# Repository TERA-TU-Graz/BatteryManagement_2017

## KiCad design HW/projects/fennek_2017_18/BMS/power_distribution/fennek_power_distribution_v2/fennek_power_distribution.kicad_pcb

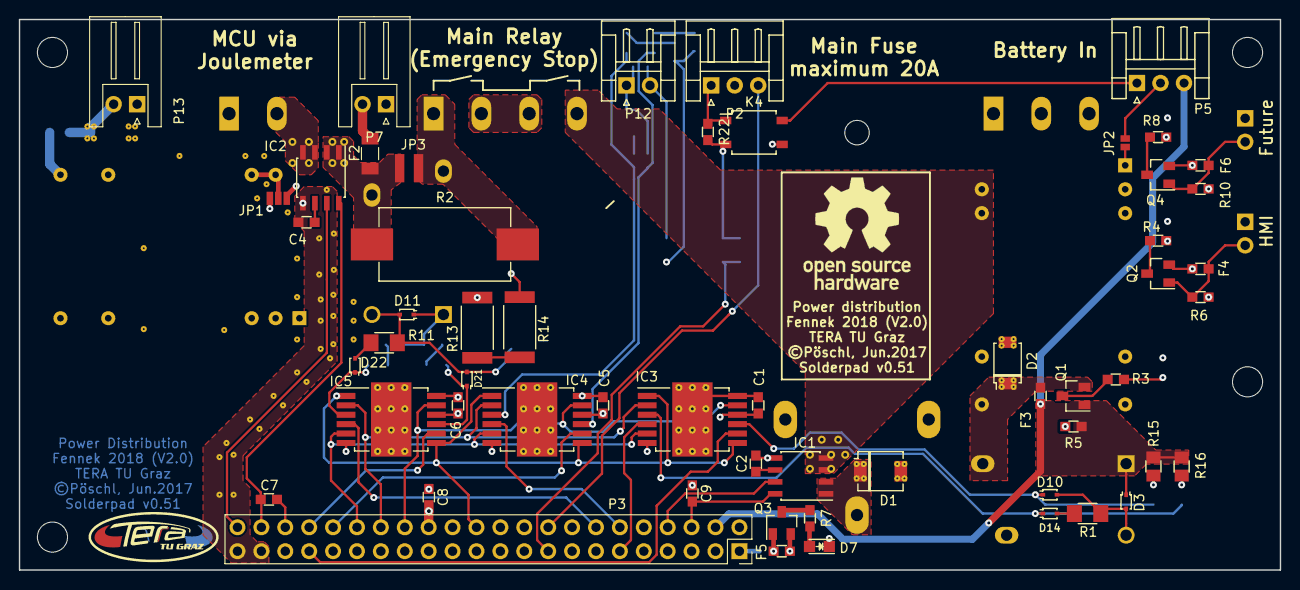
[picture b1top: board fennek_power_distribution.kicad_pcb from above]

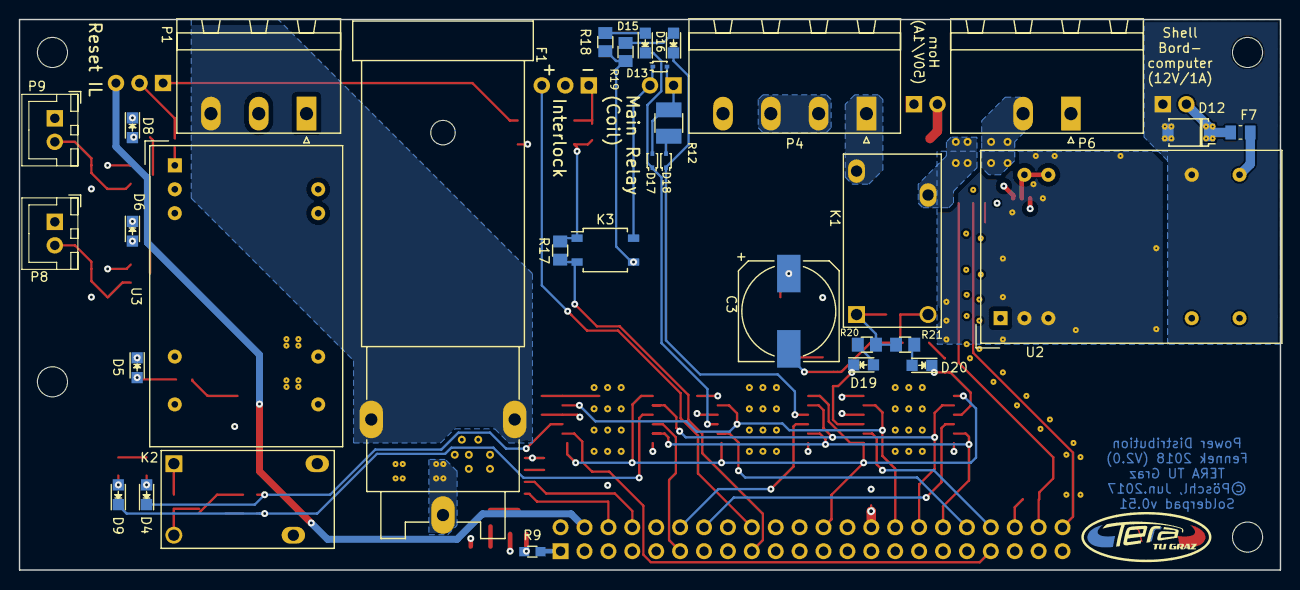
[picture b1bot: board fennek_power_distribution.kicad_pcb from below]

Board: 4 copper layers, 134.0 x 58.5 mm, 91 parts (34 on the bottom side), 71 nets.

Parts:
C1, C5, C6, C7, C8, C9: 100n; C_0603in
C2, C4: 1nf; C_0603in
C3: 820u; c_elec_10x10mm
D1: 58V; DO-214AA_with_vias_in_pad
D2, D12: 14V; SOD128_with_vias_in_pad
D3, D10, D11, D13, D14, D17, D18, D21, D22: BAS3005B-02V; BAS3005B-02V__sc79
D4, D15, D19: K_CH1; LED_0805
D5: BMS_crtl_blown; LED_0805
D6: HMI_blown; LED_0805
D7: BMS_pwr_blown; LED_0805
D8: Future_blown; LED_0805
D9, D16, D20: K_CH2; LED_0805
F1: 20A 60VDC; Fuse_holder_6.3x32mm_Schruter_0031.2520
F2: 1A 63VDC; Fuse_1206_3216Metric_Pad1.24x1.80mm_HandSolder
F3, F4, F5, F6: 0.5A 12VDC; Fuse_0603in
F7: 1A 12VDC; Fuse_0805_2012Metric_Pad1.15x1.50mm_HandSolder
IC1, IC2: ACS722LLCTR-20AB-T; ACS7xx
IC3, IC4, IC5: TLE8102SG; INF-PG-DSO-12-11-EP_N_EPvias
JP1: SEM_source; SOLDERJUMPER_3
JP2: Jumper_NO_Small; SOLDERJUMPER_2_1mm
JP3: Jumper_NO_Small; SOLDERJUMPER_2_3mm_HV
K1, K2: TE_OJ-SH-112DM; RELAIS-TE-OJ
K3: ASSR-1218; SO-4
K4: Panasonic_AQY414S; SO-4
P1: HV_in; PhoenixContact_MSTBA-G_03x5.08mm_Angled
P2: Interlock; JST_EH_S03B-EH_03x2.50mm_Angled
P3: CONN_02X22; ESW-122-12-L-D
P4: HV_Emergency_Stop_Relay; PhoenixContact_MSTBA-G_04x5.08mm_Angled
P5: Reset_Interlock; JST_EH_S03B-EH_03x2.50mm_Angled
P6: MCU_HV_supply; PhoenixContact_MSTB-GF_02x5.08mm_Angled_ThreadedFlange
P7: Horn; JST_XH_S02B-XH-A_02x2.50mm_Angled
P8: HMI_supply; JST_XH_B02B-XH-A_02x2.50mm_Straight
P9: Future_use; JST_XH_B02B-XH-A_02x2.50mm_Straight
P12: Main_relay_coil; JST_EH_S02B-EH_02x2.50mm_Angled
P13: SEM_telemetry_supply; JST_XH_S02B-XH-A_02x2.50mm_Angled
Q1, Q2, Q3, Q4: IRLML2246TRPBF-1
R1, R11: 180R; R_1206in
R2: 470R 5W; TE_SMW-5W
R3, R4, R7, R8: 12k; R_0603in
R5, R6, R9, R10: 100k; R_0603in
R12: 10R 500mW; R_1210in
R13, R14: 22R 2W; R_2512in
R15, R16, R18, R19, R20, R21: 12k; R_0805in
R17: 1k; R_0805in
R22: 1k; R_0603in
U2, U3: THD_12-4812_single_output; THD_12-xxxx
svg2mod, svg2mod#2: G***; TERA_Logo_SilkS_and_Cu_5x12.5mm

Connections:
/12VDC Bordnet/12V_Relay_Fault: IC3.4, P3.11
/12VDC Bordnet/+5V: C1.2, C5.2, C6.2, C8.2, IC3.10, IC4.10, IC5.10, P3.28
/12VDC Bordnet/+12VDC: D2.1, F3.1, K2.11, Q1.2, U3.14
/12VDC Bordnet/+12V_Future: F6.2, P9.2, Q4.1, R10.1
/12VDC Bordnet/+12V_HMI: F4.2, P8.2, Q2.1, R6.1
/12VDC Bordnet/+12V_switched: F4.1, F5.1, F6.1, K2.14, Q2.2, Q3.2, Q4.2
/12VDC Bordnet/BN_IL: K4.4, P5.1
/12VDC Bordnet/BN_on: JP2.1, P5.2
/12VDC Bordnet/IL_next-: K4.1, P2.1, R22.1
/12VDC Bordnet/Interlock_OK: IC3.1, IC3.7, IC4.1, IC4.7, IC5.1, IC5.7, P3.24
/12VDC Bordnet/LowSideSwitch_12V_Relay/CHANNEL1: D3.2, D10.2, K2.A2, R1.1
/12VDC Bordnet/LowSideSwitch_12V_Relay/CHANNEL2: D14.2, R1.2
/12VDC Bordnet/MISO: IC3.11, IC4.11, IC5.11, P3.30
/12VDC Bordnet/MOSI: IC3.2, IC4.2, IC5.2, P3.32
/12VDC Bordnet/NCS_12V_Relay: IC3.8, P3.37
/12VDC Bordnet/SCLK: IC3.5, IC4.5, IC5.5, P3.34
/12VDC telemetry/+12V_telemetry: D12.1, F7.2, P13.2
/12VDC telemetry/GND_telemetry: D12.2, P13.1, U2.16
/High voltage/+3V3: C7.2, C9.2, IC1.8, IC2.8, P3.6, P3.42
/High voltage/+HV_in: F1.2, P1.3
/High voltage/+VBatt: IC1.3, IC1.4, JP1.3, P4.4, U3.22, U3.23
/High voltage/HV+_Main_Relays: P4.2, P4.3
/High voltage/HV+_after_main_relais: JP3.1, K1.11, P4.1, R2.2
/High voltage/HV+_fused: D1.1, F1.1, IC1.1, IC1.2
/High voltage/HV+_to_MCU: IC2.3, IC2.4, P6.2
/High voltage/IL_next-: K3.1, K4.2, R17.2, R22.2
/High voltage/ISense_MCU: IC2.7, P3.44
/High voltage/ISense_Main: IC1.7, P3.8
/High voltage/LowSideSwitch_MainRelay/CHANNEL2: D18.2, R12.2
/High voltage/LowSideSwitch_PreCharge/CHANNEL2: D22.2, R11.2
/High voltage/MainRelay_Fault: IC4.4, P3.12
/High voltage/Main_Relay_A1: D13.1, K3.4, P12.2
/High voltage/Main_Relay_A2: D13.2, D17.2, P12.1, R12.1
/High voltage/NCS_MainRelay: IC4.8, P3.36
/High voltage/PreCharge_Fault: IC5.4, P3.14
/High voltage/PreCharger_A2: C3.2, D11.2, D21.2, K1.A2, R11.1
/High voltage/V+_Horn: F2.2, P7.2
/High voltage/VBatt_Switched: F2.1, IC2.1, IC2.2, JP1.1, JP3.2, K1.14, R2.1
/Master Connector/+12VDC_BMS: D3.1, F3.2, K2.A1, P3.4, P5.3, Q1.1, R5.1, R15.1, R16.1
/Master Connector/+12VDC_BMS_Switched: D11.1, F5.2, K1.A1, K3.3, P3.2, Q3.1, R9.1, R13.2, R18.1, R19.1, R20.1, R21.1
/Master Connector/IL_master+: P2.3, P3.18
/Master Connector/IL_master-: K3.2, P3.17, R17.1
/Master Connector/NCS_PreCharge: IC5.8, P3.38
GND: C1.1, C2.2, C4.2, C5.1, C6.1, C7.1, C8.1, C9.1, D1.2, D2.2, D5.1, D6.1, D7.1, D8.1, IC1.5, IC2.5, IC3.6, IC3.12, IC3.13, IC4.6, IC4.12, IC4.13, IC5.6, IC5.12, IC5.13, K4.3, P1.1, P3.1, P3.3, P3.5, P3.7, P3.9, P3.10, P3.13, P3.21, P3.22, P3.23, P3.25, P3.26, P3.27, P3.29, P3.31, P3.33, P3.35, P3.39, P3.40, P3.41, P3.43, P6.1, P7.1, P8.1, P9.1, R5.2, R6.2, R9.2, R10.2, U2.2, U2.3, U3.2, U3.3, U3.16
unnamed: C2.1, IC1.6
unnamed: C3.1, R14.1
unnamed: C4.1, IC2.6
unnamed: D4.2, R15.2
unnamed: D5.2, R3.2
unnamed: D6.2, R4.2
unnamed: D7.2, R7.2
unnamed: D8.2, R8.2
unnamed: D9.2, R16.2
unnamed: D4.1, D10.1, IC3.9
unnamed: D9.1, D14.1, IC3.3
unnamed: D15.1, D17.1, IC4.9
unnamed: D15.2, R18.2
unnamed: D16.1, D18.1, IC4.3
unnamed: D16.2, R19.2
unnamed: D19.1, D21.1, IC5.9
unnamed: D19.2, R20.2
unnamed: D20.1, D22.1, IC5.3
unnamed: D20.2, R21.2
unnamed: F7.1, U2.14
unnamed: JP1.2, U2.22, U2.23
unnamed: JP2.2, U3.1
unnamed: Q1.3, R3.1
unnamed: Q2.3, R4.1
unnamed: Q3.3, R7.1
unnamed: Q4.3, R8.1
unnamed: R13.1, R14.2

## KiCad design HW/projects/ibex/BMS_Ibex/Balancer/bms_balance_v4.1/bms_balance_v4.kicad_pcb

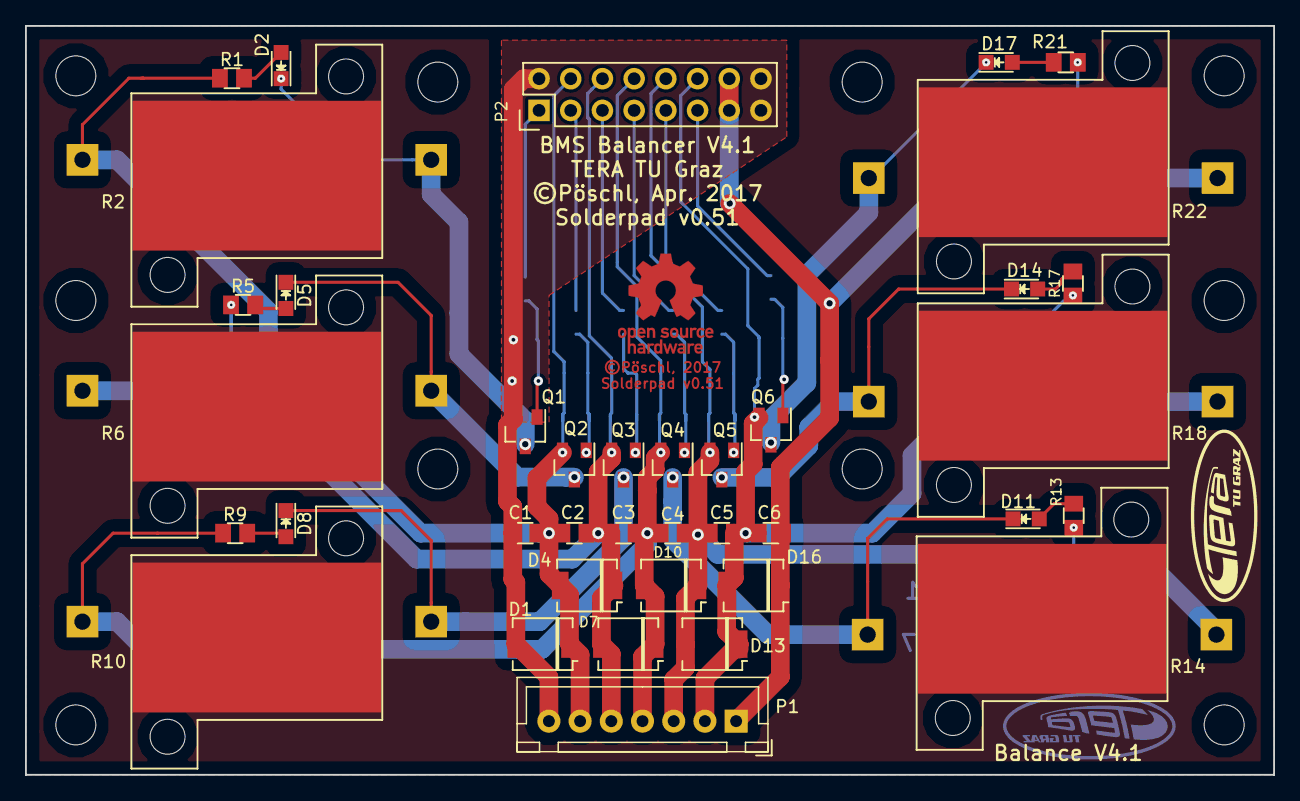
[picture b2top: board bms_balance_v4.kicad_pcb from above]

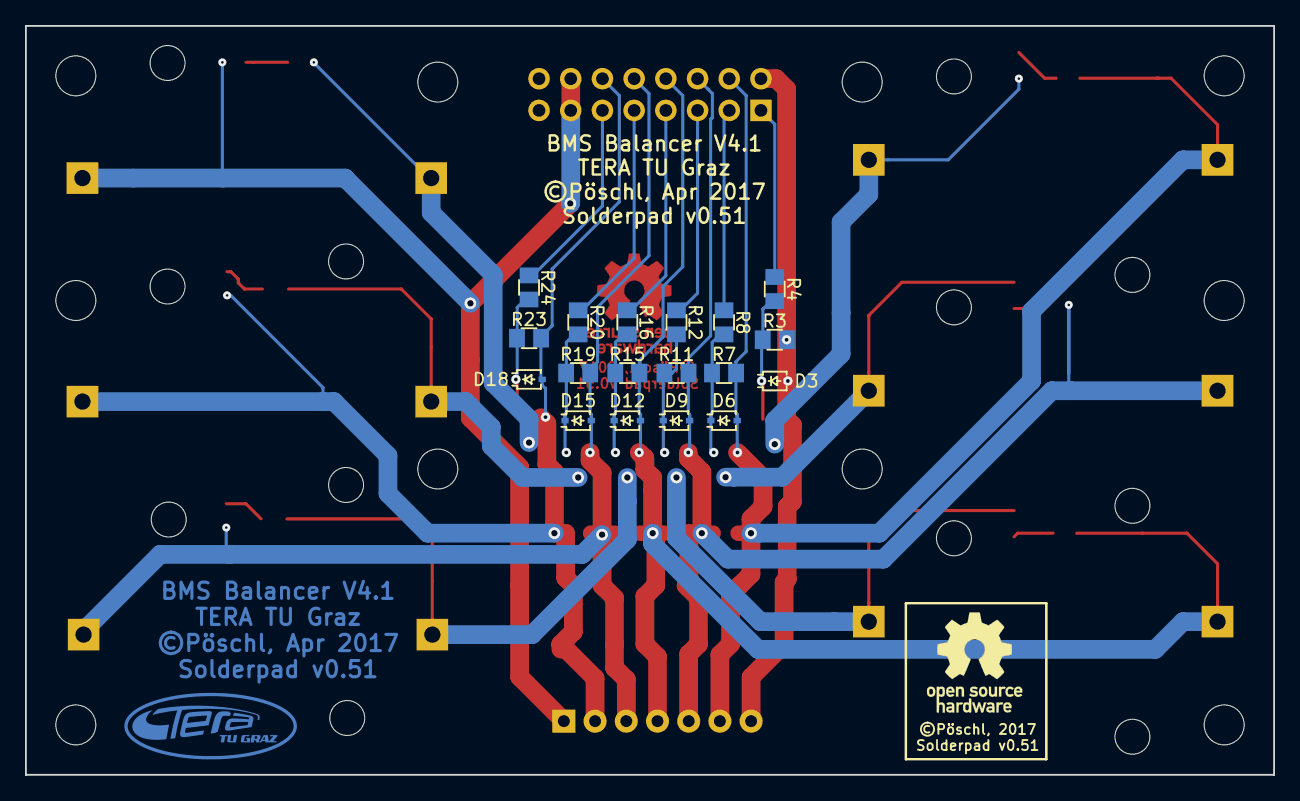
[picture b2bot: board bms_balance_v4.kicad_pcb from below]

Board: 2 copper layers, 100.0 x 60.0 mm, 58 parts (19 on the bottom side), 32 nets.

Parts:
C1, C2, C3, C4, C5, C6: 100n; C_0805in
D1, D4, D7, D10, D13, D16: 5.1V; DO-214AA
D2, D5, D8, D11, D14, D17: LED; LED_0805
D3, D6, D9, D12, D15, D18: 5.1V; SOD-323
P1: CONN_01X07; JST_XH_B07B-XH-A_07x2.50mm_Straight
P2: CONN_02X08; Pin_Header_Straight_2x08
Q1, Q2, Q3, Q4, Q5, Q6: BSS205N
R1, R5, R9, R13, R17, R21: 2K2; R_0805in
R2, R6, R10, R14, R18, R22: 3R3; R_HS15-EP
R3, R7, R11, R15, R19, R23: 2M; R_0805in
R4, R8, R12, R16, R20, R24: 1K; R_0805in
svg2mod: G***; TERA_Logo_SilkS_5x12.5mm
svg2mod#2: G***; TERA_Logo_Cu_5x12.5mm

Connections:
+BATT: C6.1, D16.1, P1.1, P2.13, P2.14, R21.1, R22.1
/BalancerCell1/Heat: R2.3, R6.3, R10.3, R14.3, R18.3, R22.3
/CB1: P2.1, R4.1
/CB2: P2.3, R8.1
/CB3: P2.5, R12.1
/CB4: P2.7, R16.1
/CB5: P2.9, R20.1
/CB6: P2.11, R24.1
/V1: C1.1, C2.2, D1.1, D4.2, D6.2, P1.6, P2.4, Q2.2, R1.1, R2.1, R7.2
/V2: C2.1, C3.2, D4.1, D7.2, D9.2, P1.5, P2.6, Q3.2, R5.1, R6.1, R11.2
/V3: C3.1, C4.2, D7.1, D10.2, D12.2, P1.4, P2.8, Q4.2, R9.1, R10.1, R15.2
/V4: C4.1, C5.2, D10.1, D13.2, D15.2, P1.3, P2.10, Q5.2, R13.1, R14.1, R19.2
/V5: C5.1, C6.2, D13.1, D16.2, D18.2, P1.2, P2.12, Q6.2, R17.1, R18.1, R23.2
GND: C1.2, D1.2, D3.2, P1.7, P2.2, P2.15, P2.16, Q1.2, R3.2
unnamed: D2.1, Q1.3, R2.2
unnamed: D2.2, R1.2
unnamed: D3.1, Q1.1, R3.1, R4.2
unnamed: D5.1, Q2.3, R6.2
unnamed: D5.2, R5.2
unnamed: D6.1, Q2.1, R7.1, R8.2
unnamed: D8.1, Q3.3, R10.2
unnamed: D8.2, R9.2
unnamed: D9.1, Q3.1, R11.1, R12.2
unnamed: D11.1, Q4.3, R14.2
unnamed: D11.2, R13.2
unnamed: D12.1, Q4.1, R15.1, R16.2
unnamed: D14.1, Q5.3, R18.2
unnamed: D14.2, R17.2
unnamed: D15.1, Q5.1, R19.1, R20.2
unnamed: D17.1, Q6.3, R22.2
unnamed: D17.2, R21.2
unnamed: D18.1, Q6.1, R23.1, R24.2

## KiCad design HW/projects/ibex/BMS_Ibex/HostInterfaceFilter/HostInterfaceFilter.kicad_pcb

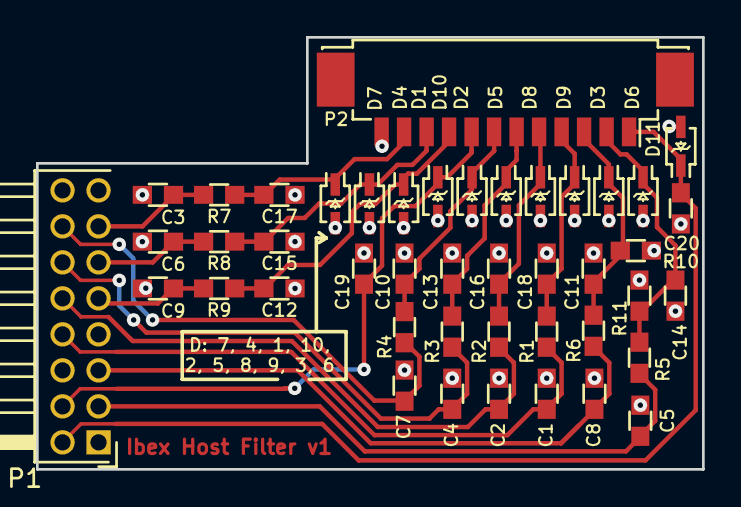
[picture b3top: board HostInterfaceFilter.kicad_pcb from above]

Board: 2 copper layers, 37.0 x 24.0 mm, 44 parts (0 on the bottom side), 21 nets.

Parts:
C1, C2, C4, C5, C7, C8, C10, C11, C13, C14, C16, C18, C19, C20: 100n; C_0603in
C3, C6, C9, C12, C15, C17: 1n; C_0603in
D1, D2, D3, D4, D5, D6, D7, D8, D9, D10: 5V; SD05_tvs_5v
D11: 15V; CDSOD323-T15S_tvs_15v
P1: FTSH-108-01-F-D-RA; Molex_87760-1616
P2: Picoblade; Molex_PicoBlade_53261-1271_12x1.25mm_Angled
R1, R2, R3, R4, R5, R6, R7, R8, R9: 1k; R_0603in
R10, R11: 10k; R_0603in

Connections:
+5V: C19.2, D10.1, P1.4, P2.8
+12V: C20.2, D11.1, P1.2, P2.1
/MISO_M: C9.2, P1.9, R9.2
/MISO_S: C12.2, D1.1, P2.9, R9.1
/MOSI_M: C6.2, P1.11, R8.2
/MOSI_S: C15.2, D4.1, P2.10, R8.1
/NCS1_M: C1.2, P1.8, R1.2
/NCS1_S: C18.2, D9.1, P2.4, R1.1
/NCS2_M: C2.2, P1.10, R2.2
/NCS2_S: C16.2, D8.1, P2.5, R2.1
/NCS3_M: C4.2, P1.12, R3.2
/NCS3_S: C13.2, D5.1, P2.6, R3.1
/NCS4_M: C7.2, P1.14, R4.2
/NCS4_S: C10.2, D2.1, P2.7, R4.1
/SCLK_M: C3.2, P1.13, R7.2
/SCLK_S: C17.2, D7.1, P2.11, R7.1
/~Alert_M: C8.2, P1.5, R6.2
/~Alert_S: C11.2, D3.1, P2.3, R6.1, R10.2
/~Fault_M: C5.2, P1.3, R5.2
/~Fault_S: C14.2, D6.1, P2.2, R5.1, R11.2
GND: C1.1, C2.1, C3.1, C4.1, C5.1, C6.1, C7.1, C8.1, C9.1, C10.1, C11.1, C12.1, C13.1, C14.1, C15.1, C16.1, C17.1, C18.1, C19.1, C20.1, D1.2, D2.2, D3.2, D4.2, D5.2, D6.2, D7.2, D8.2, D9.2, D10.2, D11.2, P1.1, P1.6, P1.7, P1.15, P1.16, P2.12, R10.1, R11.1

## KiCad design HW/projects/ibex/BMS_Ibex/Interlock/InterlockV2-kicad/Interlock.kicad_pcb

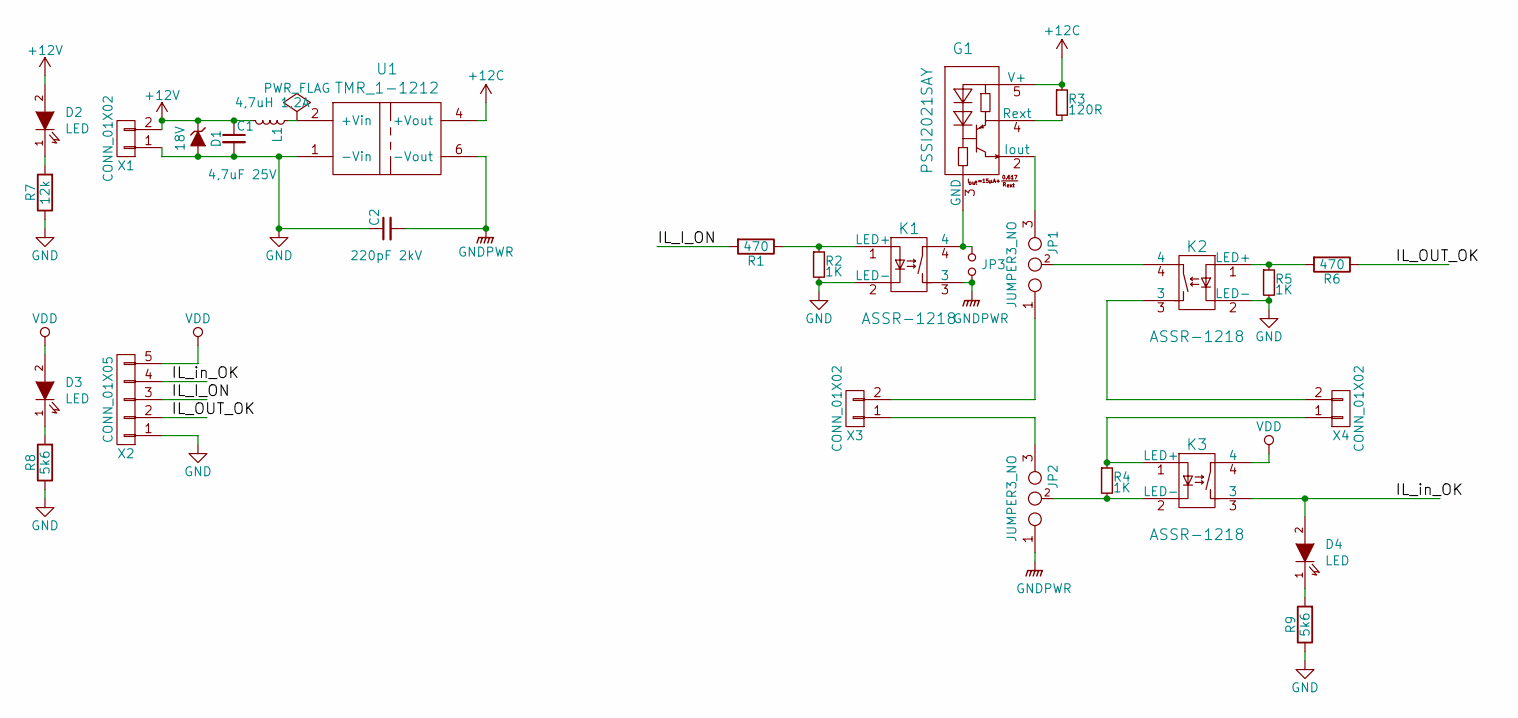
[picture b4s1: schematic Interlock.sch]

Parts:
C1: 4,7uF 25V; C_0805
C2: 220pF 2kV; C_1206in_HV
D1: 18V; DO-214AA
D2, D3, D4: LED; LED_0805
G1: PSSI2021SAY; SOT-353
JP1, JP2: JUMPER3_NO; SOLDERJUMPER_3
JP3: Jumper_NO_Small; SOLDERJUMPER_2
K1, K2, K3: ASSR-1218; SO-4
L1: 4,7uH 1,2A; L_muarta_LQH32PN
R1, R6: 470; R_0603
R2, R4, R5: 1K; R_0603
R3: 120R; R_0603
R7: 12k; R_0603
R8, R9: 5k6; R_0603
U1: TMR_1-1212; TMR_1-XX1X
X1, X3, X4: CONN_01X02; JST_XH_B02B-XH-A_02x2.50mm_Straight
X2: CONN_01X05; JST_XH_B05B-XH-A_05x2.50mm_Straight

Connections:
+12C: G1.5 (V+), R3.1, U1.4 (+Vout)
+12V: C1.1, D1.1 (K), D2.2 (A), L1.2, X1.2
/IL_I_ON: R1.2, X2.3
/IL_OUT_OK: R6.1, X2.2
/IL_in_OK: D4.2 (A), K3.3, X2.4
GND: C1.2, C2.1, D1.2 (A), K1.2 (LED-), K2.2 (LED-), R2.2, R5.2, R7.1, R8.1, R9.1, U1.1 (-Vin), X1.1, X2.1
GNDPWR: C2.2, JP2.1 (m), JP3.2, K1.3, U1.6 (-Vout)
unnamed: D2.1 (K), R7.2
unnamed: D3.1 (K), R8.2
unnamed: D4.1 (K), R9.2
unnamed: G1.2 (Iout), JP1.3
unnamed: G1.3 (GND), JP3.1, K1.4
unnamed: G1.4 (Rext), R3.2
unnamed: JP1.1 (m), X3.2
unnamed: JP1.2, K2.4
unnamed: JP2.2, K3.2 (LED-), R4.2
unnamed: JP2.3, X3.1
unnamed: K1.1 (LED+), R1.1, R2.1
unnamed: K2.1 (LED+), R5.1, R6.2
unnamed: K2.3, X4.2
unnamed: K3.1 (LED+), R4.1, X4.1
unnamed: L1.1, U1.2 (+Vin)
VDD: D3.2 (A), K3.4, X2.5

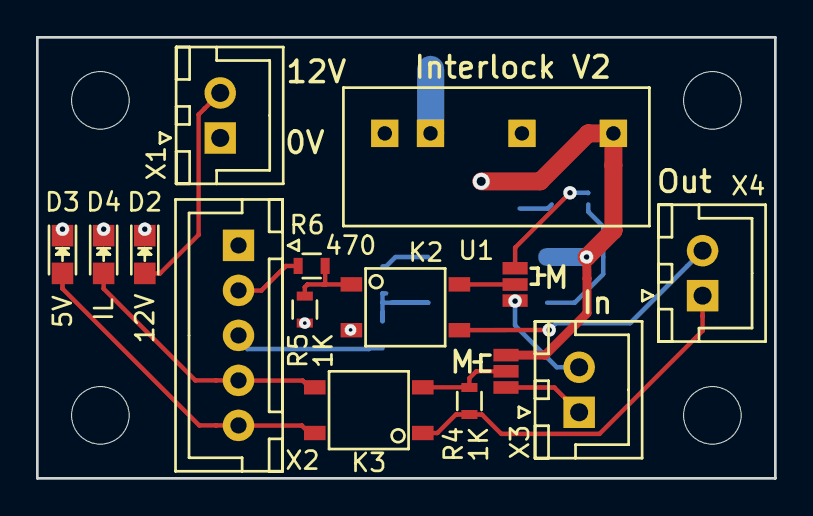
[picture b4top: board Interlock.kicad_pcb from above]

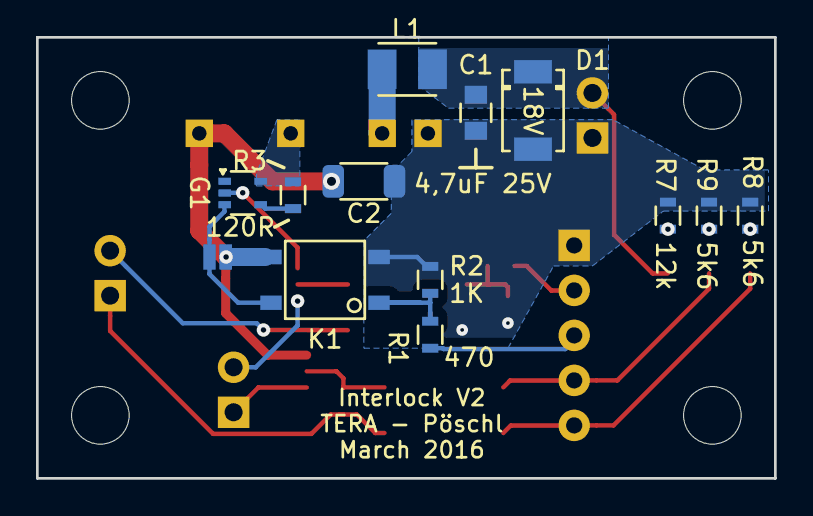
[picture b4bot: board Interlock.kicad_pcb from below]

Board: 2 copper layers, 41.0 x 24.5 mm, 28 parts (13 on the bottom side), 23 nets.

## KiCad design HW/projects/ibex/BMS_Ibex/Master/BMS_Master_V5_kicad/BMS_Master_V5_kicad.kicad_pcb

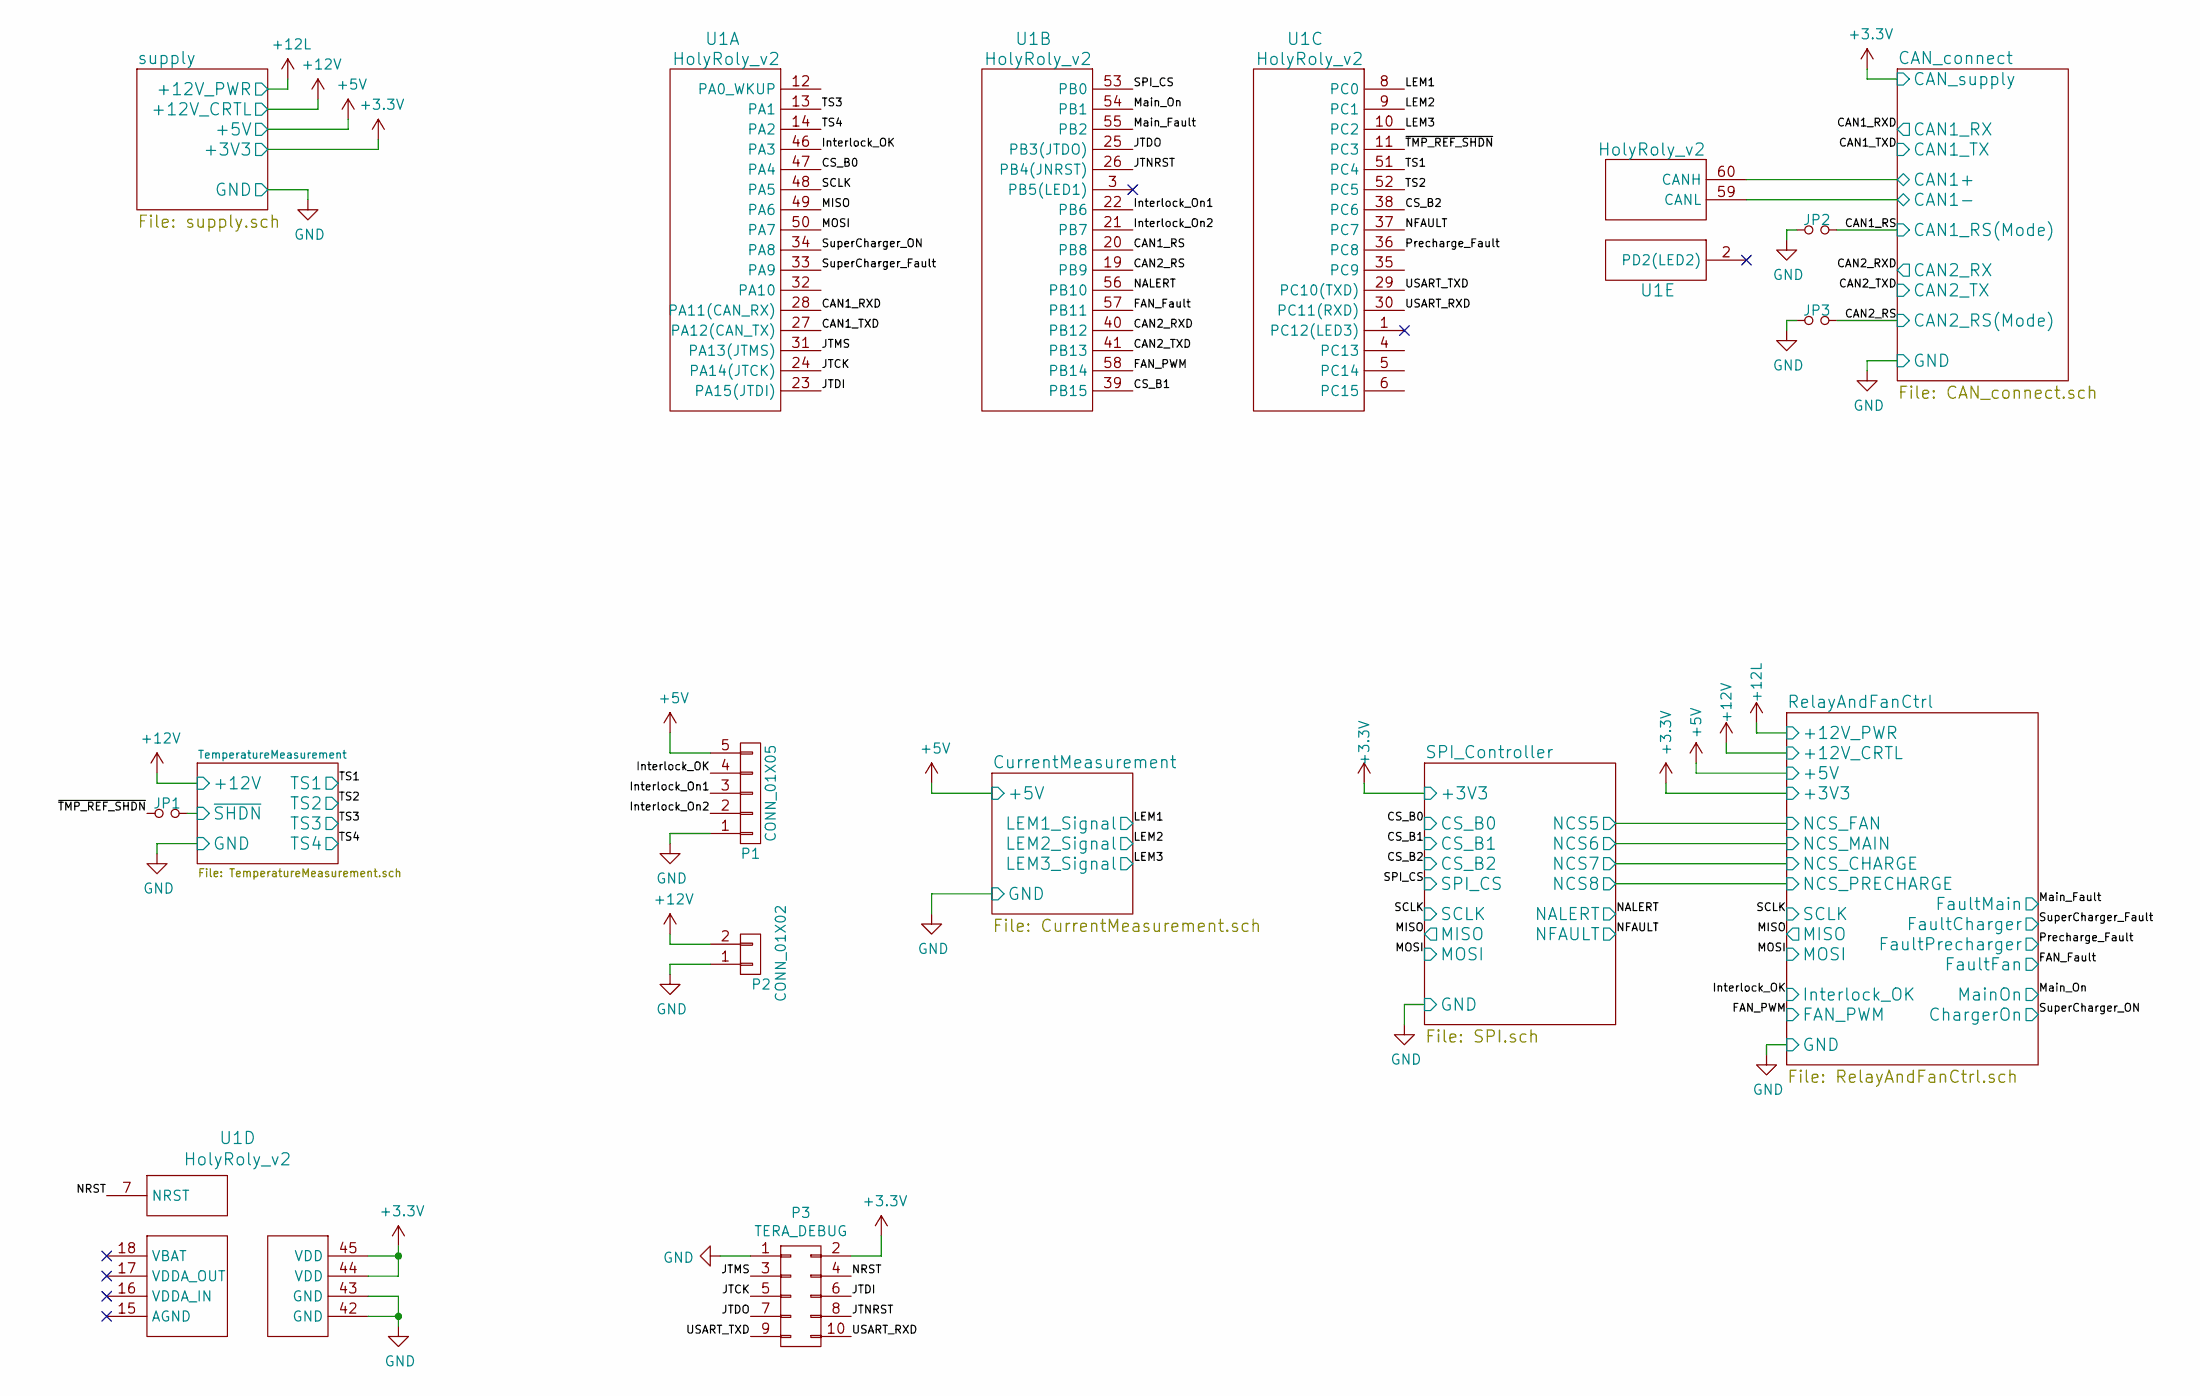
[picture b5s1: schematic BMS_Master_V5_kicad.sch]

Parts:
JP1, JP2, JP3: Jumper_NO_Small; SOLDERJUMPER_2
P1: CONN_01X05; JST_XH_B05B-XH-A_05x2.50mm_Straight
P2: CONN_01X02; JST_XH_B02B-XH-A_02x2.50mm_Straight
P3: TERA_DEBUG
U1: HolyRoly_v2

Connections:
+3V3: P3.2, U1.44 (VDD), U1.45 (VDD); also elsewhere on the board
+5V: P1.5; also elsewhere on the board
+12V: P2.2; also elsewhere on the board
/CAN1_RS: JP2.2, U1.20 (PB8); also elsewhere on the board
/CAN1_RXD: U1.28 (PA11(CAN_RX)); also elsewhere on the board
/CAN1_TXD: U1.27 (PA12(CAN_TX)); also elsewhere on the board
/CAN2_RS: JP3.2, U1.19 (PB9); also elsewhere on the board
/CAN2_RXD: U1.40 (PB12); also elsewhere on the board
/CAN2_TXD: U1.41 (PB13); also elsewhere on the board
/CAN_connect/CAN1+: U1.60 (CANH); also elsewhere on the board
/CAN_connect/CAN1-: U1.59 (CANL); also elsewhere on the board
/CS_B0: U1.47 (PA4); also elsewhere on the board
/CS_B1: U1.39 (PB15); also elsewhere on the board
/CS_B2: U1.38 (PC6); also elsewhere on the board
/FAN_Fault: U1.57 (PB11); also elsewhere on the board
/FAN_PWM: U1.58 (PB14); also elsewhere on the board
/Interlock_OK: P1.4, U1.46 (PA3); also elsewhere on the board
/Interlock_On1: P1.3, U1.22 (PB6)
/Interlock_On2: P1.2, U1.21 (PB7)
/JTCK: P3.5, U1.24 (PA14(JTCK))
/JTDI: P3.6, U1.23 (PA15(JTDI))
/JTDO: P3.7, U1.25 (PB3(JTDO))
/JTMS: P3.3, U1.31 (PA13(JTMS))
/JTNRST: P3.8, U1.26 (PB4(JNRST))
/LEM1: U1.8 (PC0); also elsewhere on the board
/LEM2: U1.9 (PC1); also elsewhere on the board
/LEM3: U1.10 (PC2); also elsewhere on the board
/MISO: U1.49 (PA6); also elsewhere on the board
/MOSI: U1.50 (PA7); also elsewhere on the board
/Main_Fault: U1.55 (PB2); also elsewhere on the board
/Main_On: U1.54 (PB1); also elsewhere on the board
/NALERT: U1.56 (PB10); also elsewhere on the board
/NFAULT: U1.37 (PC7); also elsewhere on the board
/NRST: P3.4, U1.7 (NRST)
/Precharge_Fault: U1.36 (PC8); also elsewhere on the board
/SCLK: U1.48 (PA5); also elsewhere on the board
/SPI_CS: U1.53 (PB0); also elsewhere on the board
/SuperCharger_Fault: U1.33 (PA9); also elsewhere on the board
/SuperCharger_ON: U1.34 (PA8); also elsewhere on the board
/TS1: U1.51 (PC4); also elsewhere on the board
/TS2: U1.52 (PC5); also elsewhere on the board
/TS3: U1.13 (PA1); also elsewhere on the board
/TS4: U1.14 (PA2); also elsewhere on the board
/TemperatureMeasurement/~SHDN: JP1.2; also elsewhere on the board
/USART_RXD: P3.10, U1.30 (PC11(RXD))
/USART_TXD: P3.9, U1.29 (PC10(TXD))
/~TMP_REF_SHDN: JP1.1, U1.11 (PC3)
GND: JP2.1, JP3.1, P1.1, P2.1, P3.1, U1.42 (GND), U1.43 (GND); also elsewhere on the board

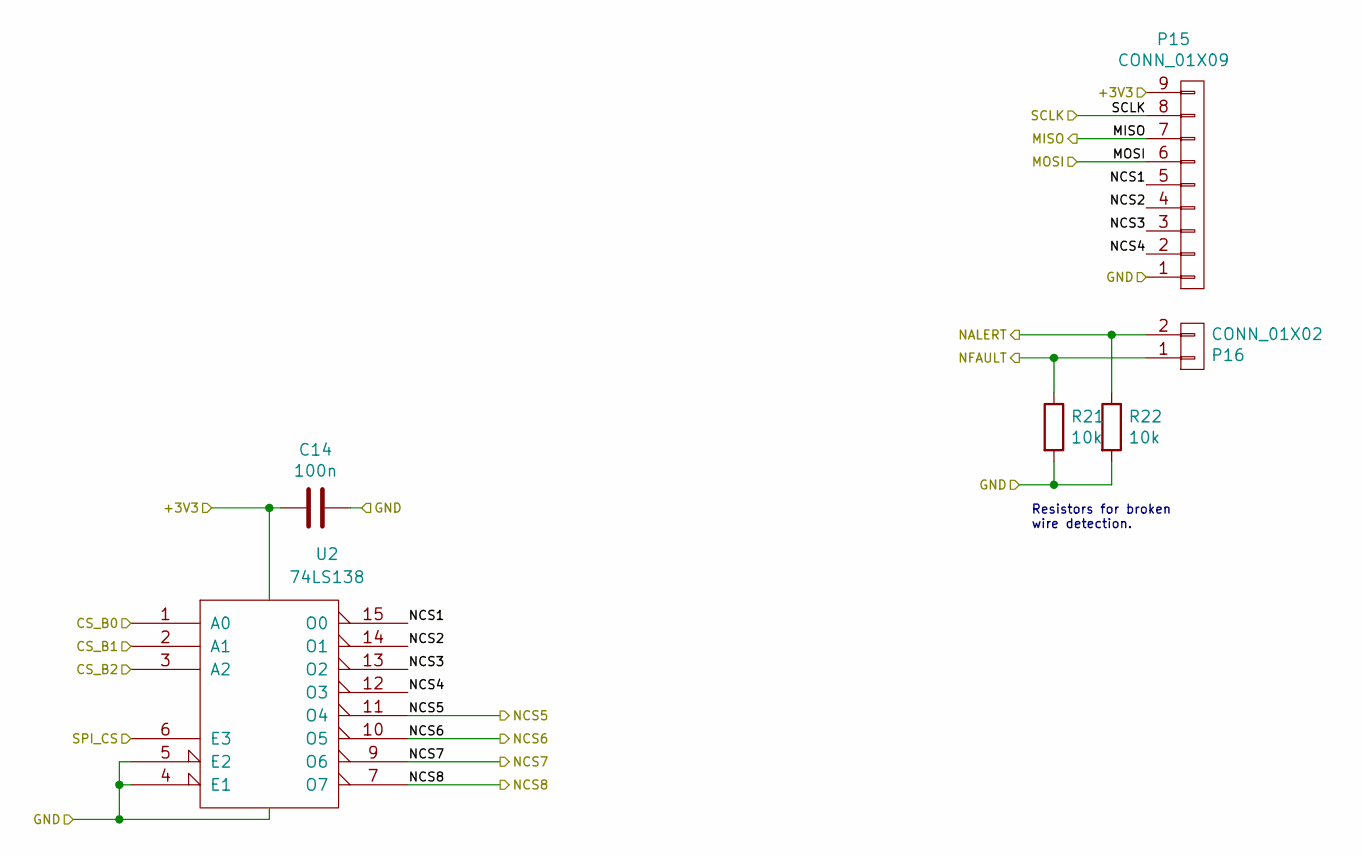
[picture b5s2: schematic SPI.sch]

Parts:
C14: 100n; C_0603
P15: CONN_01X09; Molex_PicoBlade_53398-0971
P16: CONN_01X02; JST_XH_B02B-XH-A_02x2.50mm_Straight
R21, R22: 10k; R_0805
U2: 74LS138; SOIC-16_3.9x9.9mm_Pitch1.27mm

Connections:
+3V3: C14.2, P15.9, U2.16 (VCC); also elsewhere on the board
/CS_B0: U2.1 (A0); also elsewhere on the board
/CS_B1: U2.2 (A1); also elsewhere on the board
/CS_B2: U2.3 (A2); also elsewhere on the board
/MISO: P15.7; also elsewhere on the board
/MOSI: P15.6; also elsewhere on the board
/NALERT: P16.2, R22.1; also elsewhere on the board
/NFAULT: P16.1, R21.1; also elsewhere on the board
/SCLK: P15.8; also elsewhere on the board
/SPI_CS: U2.6 (E3); also elsewhere on the board
/SPI_Controller/NCS1: P15.5, U2.15 (O0)
/SPI_Controller/NCS2: P15.4, U2.14 (O1)
/SPI_Controller/NCS3: P15.3, U2.13 (O2)
/SPI_Controller/NCS4: P15.2, U2.12 (O3)
/SPI_Controller/NCS5: U2.11 (O4); also elsewhere on the board
/SPI_Controller/NCS6: U2.10 (O5); also elsewhere on the board
/SPI_Controller/NCS7: U2.9 (O6); also elsewhere on the board
/SPI_Controller/NCS8: U2.7 (O7); also elsewhere on the board
GND: C14.1, P15.1, R21.2, R22.2, U2.4 (E1), U2.5 (E2), U2.8 (GND); also elsewhere on the board

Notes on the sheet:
Resistors for broken wire detection.

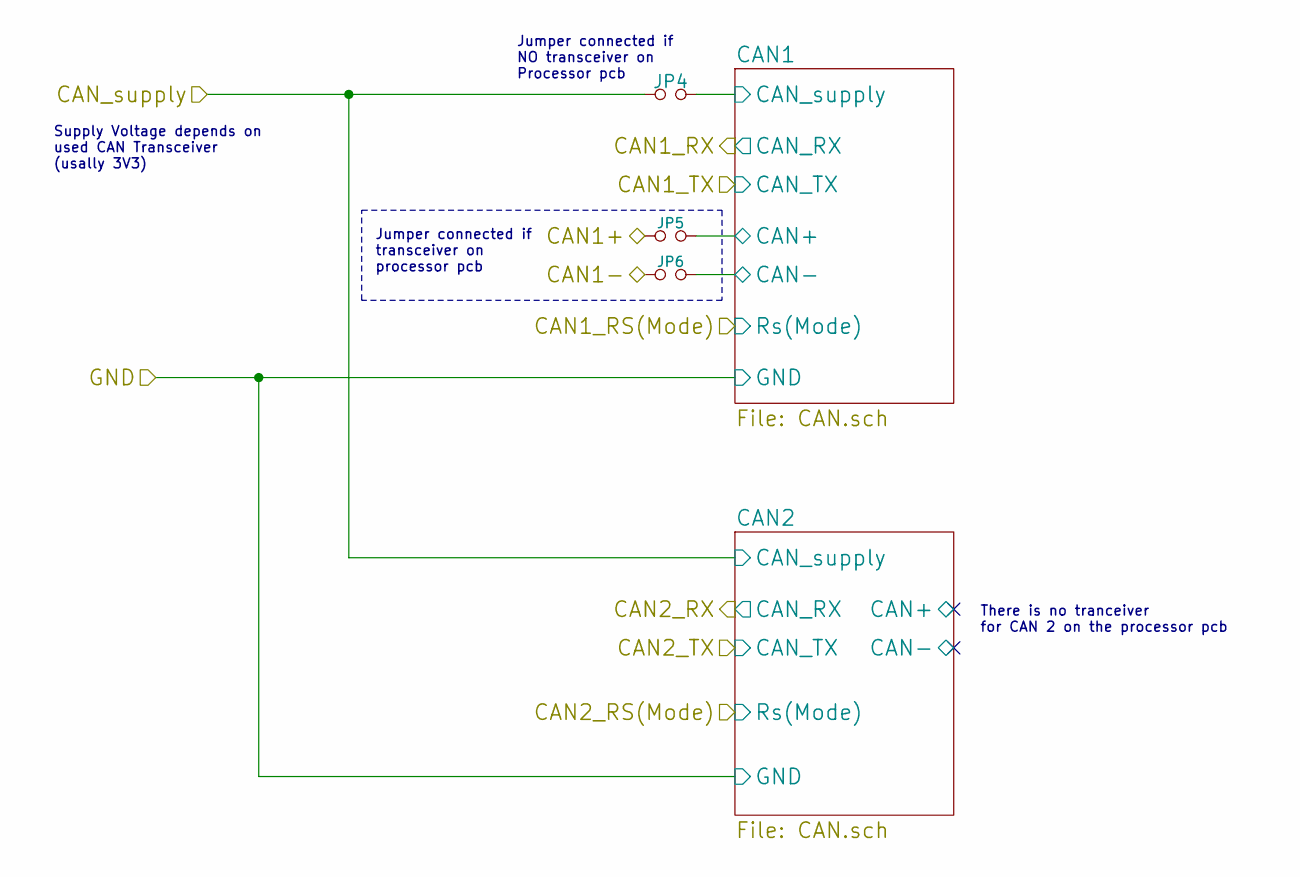
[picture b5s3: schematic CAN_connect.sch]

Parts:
JP4, JP5, JP6: Jumper_NO_Small; SOLDERJUMPER_2

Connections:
+3V3: JP4.1; also elsewhere on the board
/CAN_connect/CAN1+: JP5.1; also elsewhere on the board
/CAN_connect/CAN1-: JP6.1; also elsewhere on the board
/CAN_connect/CAN1/CAN+: JP5.2; also elsewhere on the board
/CAN_connect/CAN1/CAN-: JP6.2; also elsewhere on the board
/CAN_connect/CAN1/CAN_supply: JP4.2; also elsewhere on the board

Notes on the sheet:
Supply Voltage depends on used CAN Transceiver (usally 3V3)
Jumper connected if NO transceiver on Processor pcb
Jumper connected if transceiver on processor pcb
There is no tranceiver for CAN 2 on the processor pcb

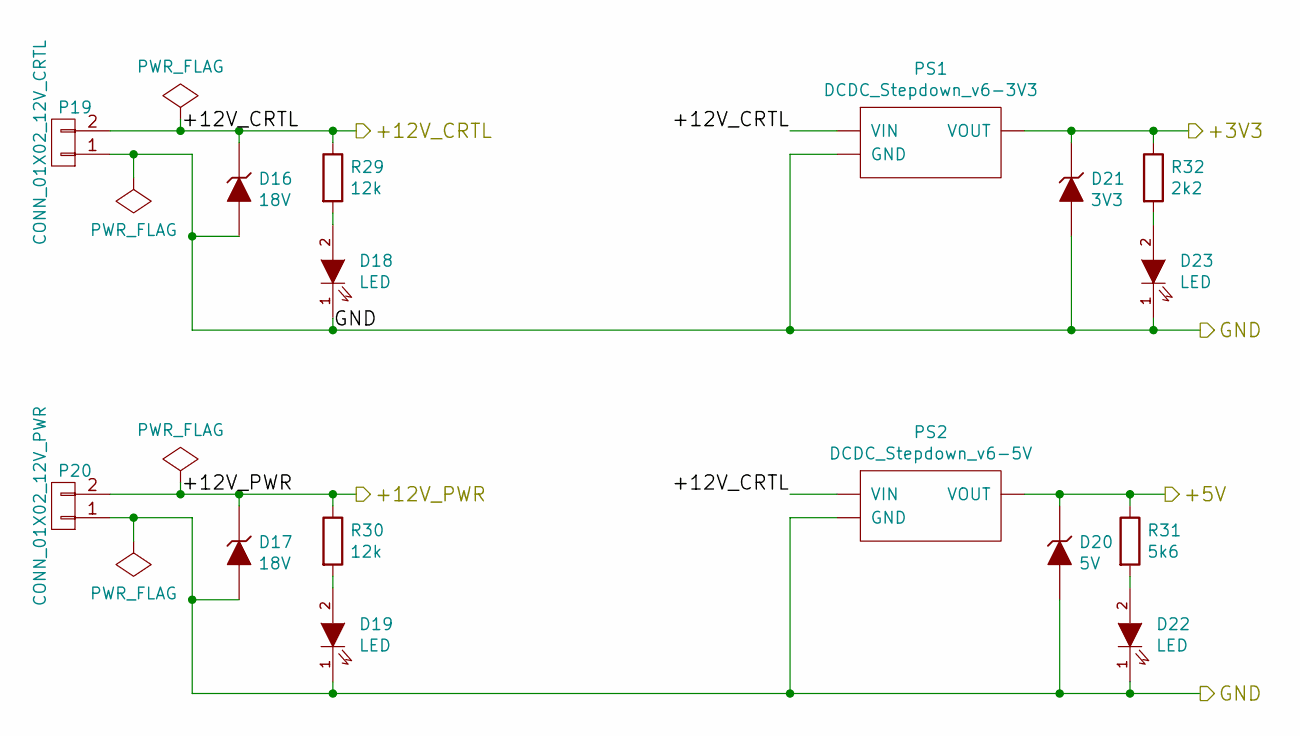
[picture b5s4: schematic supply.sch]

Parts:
D16, D17: 18V; DO-214AA_with_vias_in_pad
D18, D19, D22, D23: LED; LED_0805
D20: 5V; DO-216AA
D21: 3V3; DO-216AA
P19: CONN_01X02_12V_CRTL; JST_XH_B02B-XH-A_02x2.50mm_Straight
P20: CONN_01X02_12V_PWR; MCV_1.5_2-GF-3.5
PS1: DCDC_Stepdown_v6-3V3; DCDC_Stepdown_v6
PS2: DCDC_Stepdown_v6-5V; DCDC_Stepdown_v6
R29, R30: 12k; R_0805
R31: 5k6; R_0805
R32: 2k2; R_0805

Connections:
+3V3: D21.1 (K), PS1.2 (VOUT), R32.1; also elsewhere on the board
+5V: D20.1 (K), PS2.2 (VOUT), R31.1; also elsewhere on the board
+12L: D17.1 (K), P20.2, R30.1; also elsewhere on the board
+12V: D16.1 (K), P19.2, PS1.1 (VIN), PS2.1 (VIN), R29.1; also elsewhere on the board
GND: D16.2 (A), D17.2 (A), D18.1 (K), D19.1 (K), D20.2 (A), D21.2 (A), D22.1 (K), D23.1 (K), P19.1, P20.1, PS1.3 (GND), PS1.4 (GND), PS2.3 (GND), PS2.4 (GND); also elsewhere on the board
unnamed: D18.2 (A), R29.2
unnamed: D19.2 (A), R30.2
unnamed: D22.2 (A), R31.2
unnamed: D23.2 (A), R32.2

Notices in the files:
HW/projects/fennek_2017_18/BMS/power_distribution/fennek_power_distribution_v2/fennek_power_distribution.kicad_pcb:
©Pöschl, Jun.2017
HW/projects/ibex/BMS_Ibex/Balancer/bms_balance_v4.1/bms_balance_v4.kicad_pcb:
©Pöschl, Apr 2017
©Pöschl, 2017
parts and their libraries:
SparkFun: Licensing: CC v3.0 Share-Alike You are welcome to use this library for commercial purposes.
